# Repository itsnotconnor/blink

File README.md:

# Simple LED Blink PCB with RP2040

## Features
* RP2040 Bootloader switch
* Single WS2182 RGB LED w/ logic level shifter
* ADC inputs for future sensors
* GPIO breakout
* Program Port

## Design reference from raspberry pi
* https://datasheets.raspberrypi.com/rp2040/hardware-design-with-rp2040.pdf

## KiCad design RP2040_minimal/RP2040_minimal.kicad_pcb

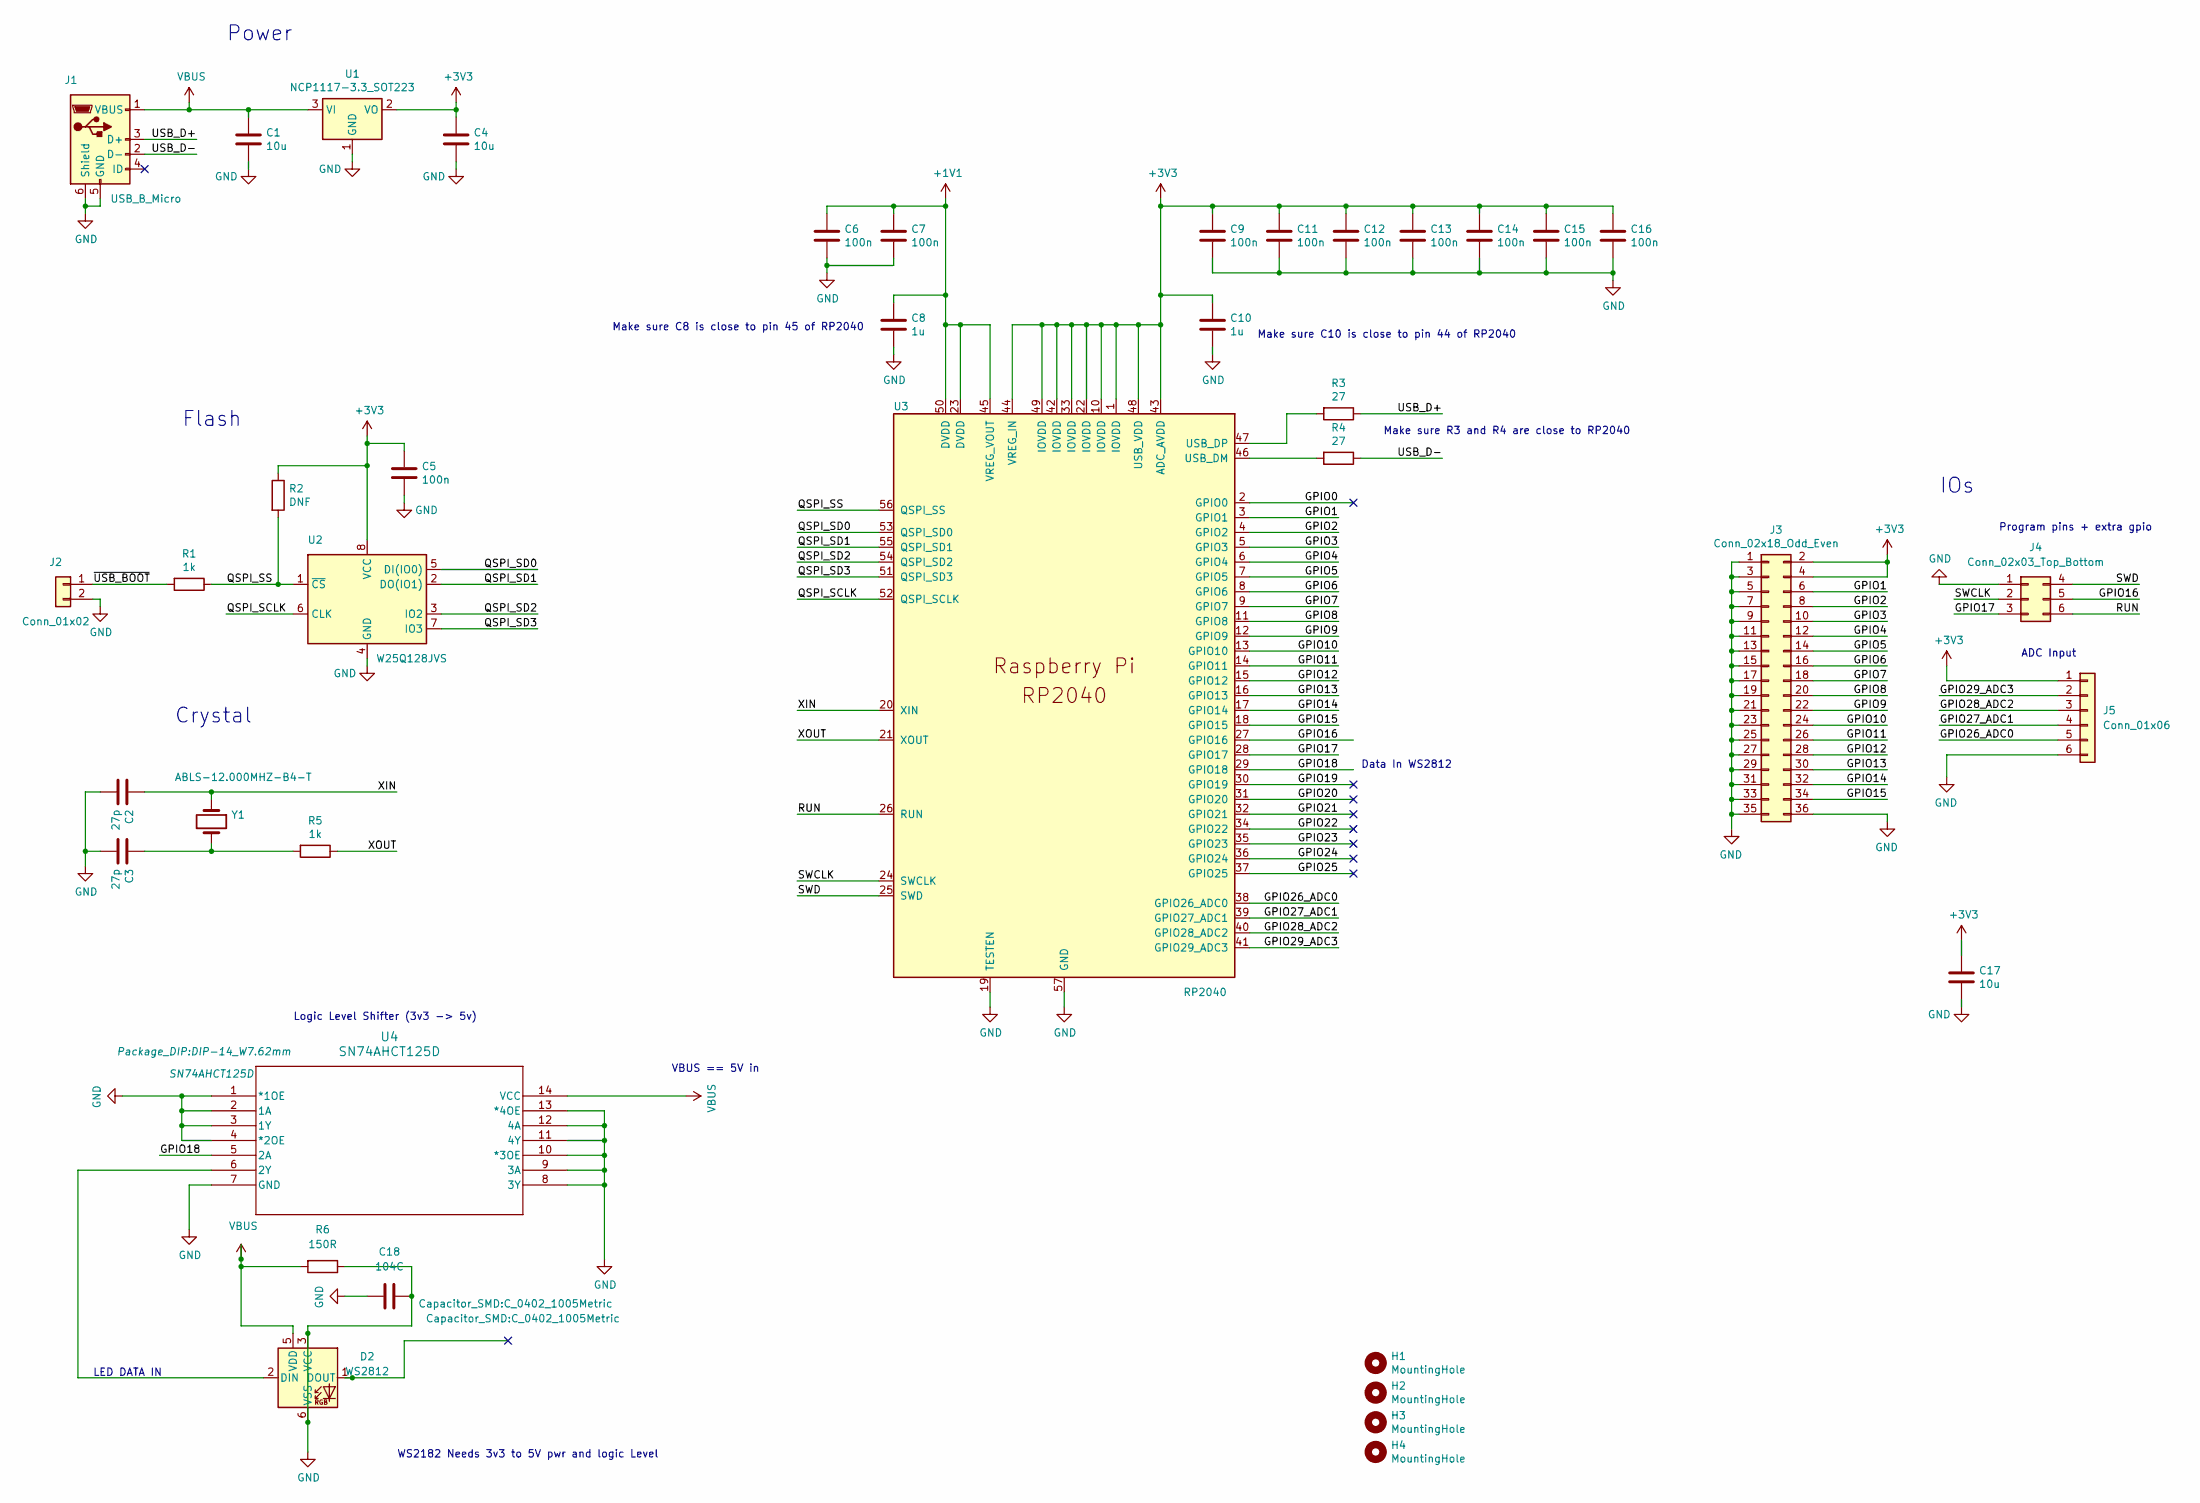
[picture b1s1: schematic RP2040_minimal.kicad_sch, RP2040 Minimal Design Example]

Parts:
C1, C4, C17: 10u; C_0805_2012Metric
C2, C3: 27p; C_0402_1005Metric
C5, C6, C7, C9, C11, C12, C13, C14, C15, C16: 100n; C_0402_1005Metric
C8, C10: 1u; C_0402_1005Metric
C18: 104C; C_0402_1005Metric
D2: WS2812; LED_WS2812_PLCC6_5.0x5.0mm_P1.6mm
H1, H2, H3, H4: MountingHole; MountingHole_2.7mm_M2.5
J1: USB_B_Micro; USB_Micro-B_Amphenol_10103594-0001LF_Horizontal_modified
J2: Conn_01x02; PinHeader_1x02_P2.54mm_Vertical
J3: Conn_02x18_Odd_Even; PinHeader_2x18_P2.54mm_Vertical
J4: Conn_02x03_Top_Bottom; PinHeader_2x03_P2.54mm_Horizontal
J5: Conn_01x06; PinHeader_1x06_P2.54mm_Vertical
R1, R5: 1k; C_0402_1005Metric
R2: DNF; C_0402_1005Metric
R3, R4: 27; C_0402_1005Metric
R6: 150R; C_0402_1005Metric
U1: NCP1117-3.3_SOT223; SOT-223-3_TabPin2
U2: W25Q128JVS; SOIC-8_5.23x5.23mm_P1.27mm
U3: RP2040; RP2040-QFN-56
U4: SN74AHCT125D; DIP-14_W7.62mm
Y1: ABLS-12.000MHZ-B4-T; Crystal_SMD_HC49-US

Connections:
+1V1: C6.1, C7.1, C8.1, U3.23 (DVDD), U3.45 (VREG_VOUT), U3.50 (DVDD)
+3V3: C4.1, C5.1, C9.1, C10.1, C11.1, C12.1, C13.1, C14.1, C15.1, C16.1, C17.1, J3.2, J3.4, J5.1, R2.1, U1.2 (VO), U2.8 (VCC), U3.1 (IOVDD), U3.10 (IOVDD), U3.22 (IOVDD), U3.33 (IOVDD), U3.42 (IOVDD), U3.43 (ADC_AVDD), U3.44 (VREG_IN), U3.48 (USB_VDD), U3.49 (IOVDD)
/GPIO0: U3.2 (GPIO0)
/GPIO1: J3.6, U3.3 (GPIO1)
/GPIO2: J3.8, U3.4 (GPIO2)
/GPIO3: J3.10, U3.5 (GPIO3)
/GPIO4: J3.12, U3.6 (GPIO4)
/GPIO5: J3.14, U3.7 (GPIO5)
/GPIO6: J3.16, U3.8 (GPIO6)
/GPIO7: J3.18, U3.9 (GPIO7)
/GPIO8: J3.20, U3.11 (GPIO8)
/GPIO9: J3.22, U3.12 (GPIO9)
/GPIO10: J3.24, U3.13 (GPIO10)
/GPIO11: J3.26, U3.14 (GPIO11)
/GPIO12: J3.28, U3.15 (GPIO12)
/GPIO13: J3.30, U3.16 (GPIO13)
/GPIO14: J3.32, U3.17 (GPIO14)
/GPIO15: J3.34, U3.18 (GPIO15)
/GPIO16: J4.5, U3.27 (GPIO16)
/GPIO17: J4.3, U3.28 (GPIO17)
/GPIO18: U3.29 (GPIO18), U4.5 (2A)
/GPIO19: U3.30 (GPIO19)
/GPIO20: U3.31 (GPIO20)
/GPIO21: U3.32 (GPIO21)
/GPIO22: U3.34 (GPIO22)
/GPIO23: U3.35 (GPIO23)
/GPIO24: U3.36 (GPIO24)
/GPIO25: U3.37 (GPIO25)
/GPIO26_ADC0: J5.5, U3.38 (GPIO26_ADC0)
/GPIO27_ADC1: J5.4, U3.39 (GPIO27_ADC1)
/GPIO28_ADC2: J5.3, U3.40 (GPIO28_ADC2)
/GPIO29_ADC3: J5.2, U3.41 (GPIO29_ADC3)
/QSPI_SCLK: U2.6 (CLK), U3.52 (QSPI_SCLK)
/QSPI_SD0: U2.5 (DI(IO0)), U3.53 (QSPI_SD0)
/QSPI_SD1: U2.2 (DO(IO1)), U3.55 (QSPI_SD1)
/QSPI_SD2: U2.3 (IO2), U3.54 (QSPI_SD2)
/QSPI_SD3: U2.7 (IO3), U3.51 (QSPI_SD3)
/QSPI_SS: R1.1, R2.2, U2.1 (~CS), U3.56 (QSPI_SS)
/RUN: J4.6, U3.26 (RUN)
/SWCLK: J4.2, U3.24 (SWCLK)
/SWD: J4.4, U3.25 (SWD)
/USB_D+: J1.3 (D+), R3.1
/USB_D-: J1.2 (D-), R4.1
/XIN: C2.1, U3.20 (XIN), Y1.1
/XOUT: R5.1, U3.21 (XOUT)
/~USB_BOOT: J2.1, R1.2
GND: C1.2, C2.2, C3.2, C4.2, C5.2, C6.2, C7.2, C8.2, C9.2, C10.2, C11.2, C12.2, C13.2, C14.2, C15.2, C16.2, C17.2, C18.1, C18.2, D2.3 (VCC), D2.6 (VSS), J1.5 (GND), J1.6 (Shield), J2.2, J3.1, J3.3, J3.5, J3.7, J3.9, J3.11, J3.13, J3.15, J3.17, J3.19, J3.21, J3.23, J3.25, J3.27, J3.29, J3.31, J3.33, J3.35, J3.36, J4.1, J5.6, R6.1, U1.1 (GND), U2.4 (GND), U3.19 (TESTEN), U3.57 (GND), U4.1 (*1OE), U4.2 (1A), U4.3 (1Y), U4.4 (*2OE), U4.7 (GND), U4.8 (3Y), U4.9 (3A), U4.10 (*3OE), U4.11 (4Y), U4.12 (4A), U4.13 (*4OE)
unnamed: C3.1, R5.2, Y1.2
unnamed: D2.2 (DIN), U4.6 (2Y)
unnamed: R4.2, U3.46 (USB_DM)
unnamed: R3.2, U3.47 (USB_DP)
VBUS: C1.1, D2.5 (VDD), J1.1 (VBUS), R6.2, U1.3 (VI), U4.14 (VCC)

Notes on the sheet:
ADC Input
LED DATA IN
Logic Level Shifter (3v3 -> 5v)
Make sure C10 is close to pin 44 of RP2040
Make sure C8 is close to pin 45 of RP2040
Crystal
Data In WS2812
WS2182 Needs 3v3 to 5V pwr and logic Level
Program pins + extra gpio
Flash
Make sure R3 and R4 are close to RP2040
IOs
Power
VBUS == 5V in

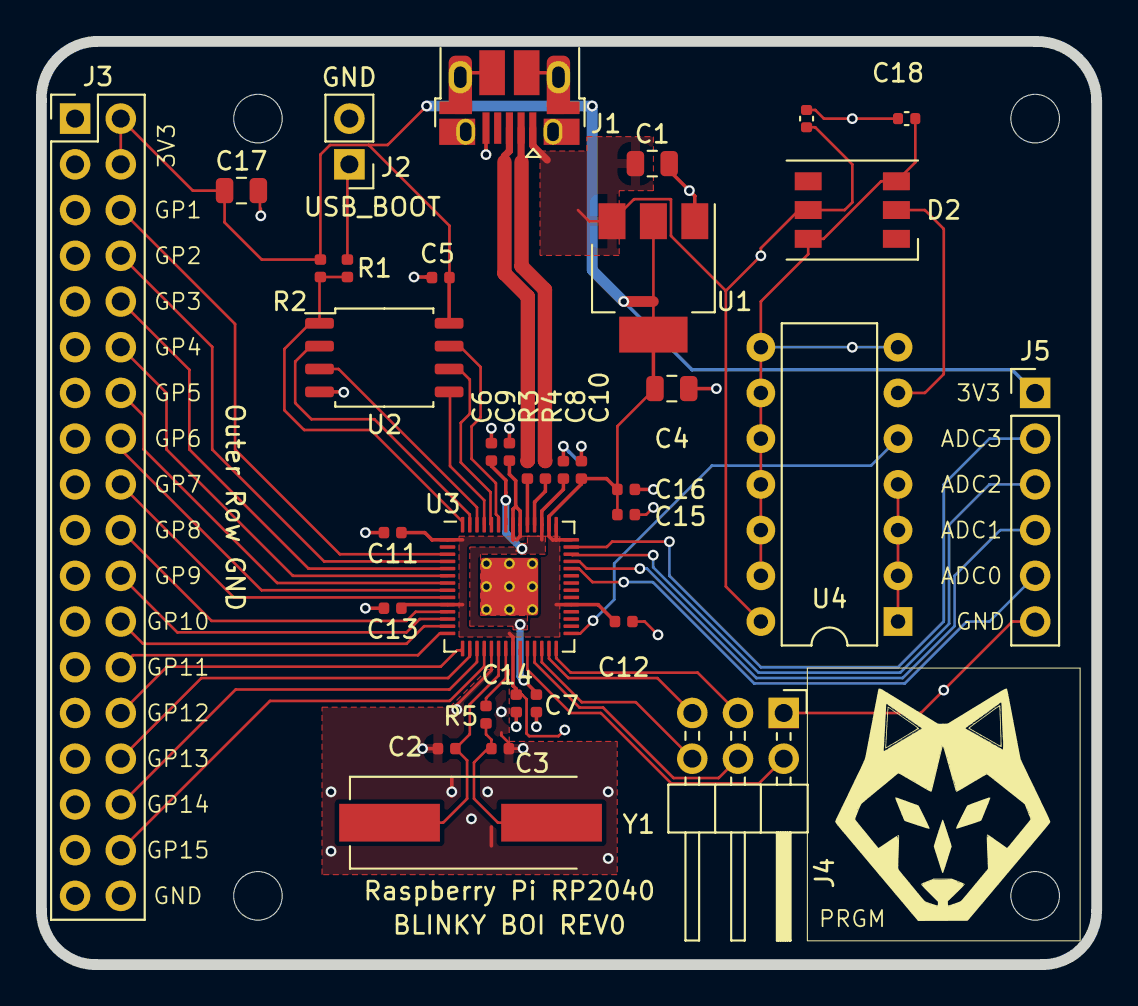
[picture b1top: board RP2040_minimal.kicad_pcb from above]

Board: 2 copper layers, 58.6 x 51.3 mm, 39 parts (0 on the bottom side), 44 nets.

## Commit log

2024-02-17 init blinky boi
2024-02-18 moved logo and resolved schematic DRC
2024-02-18 moved digital led trace to back of board
2024-02-19 Created README.md
